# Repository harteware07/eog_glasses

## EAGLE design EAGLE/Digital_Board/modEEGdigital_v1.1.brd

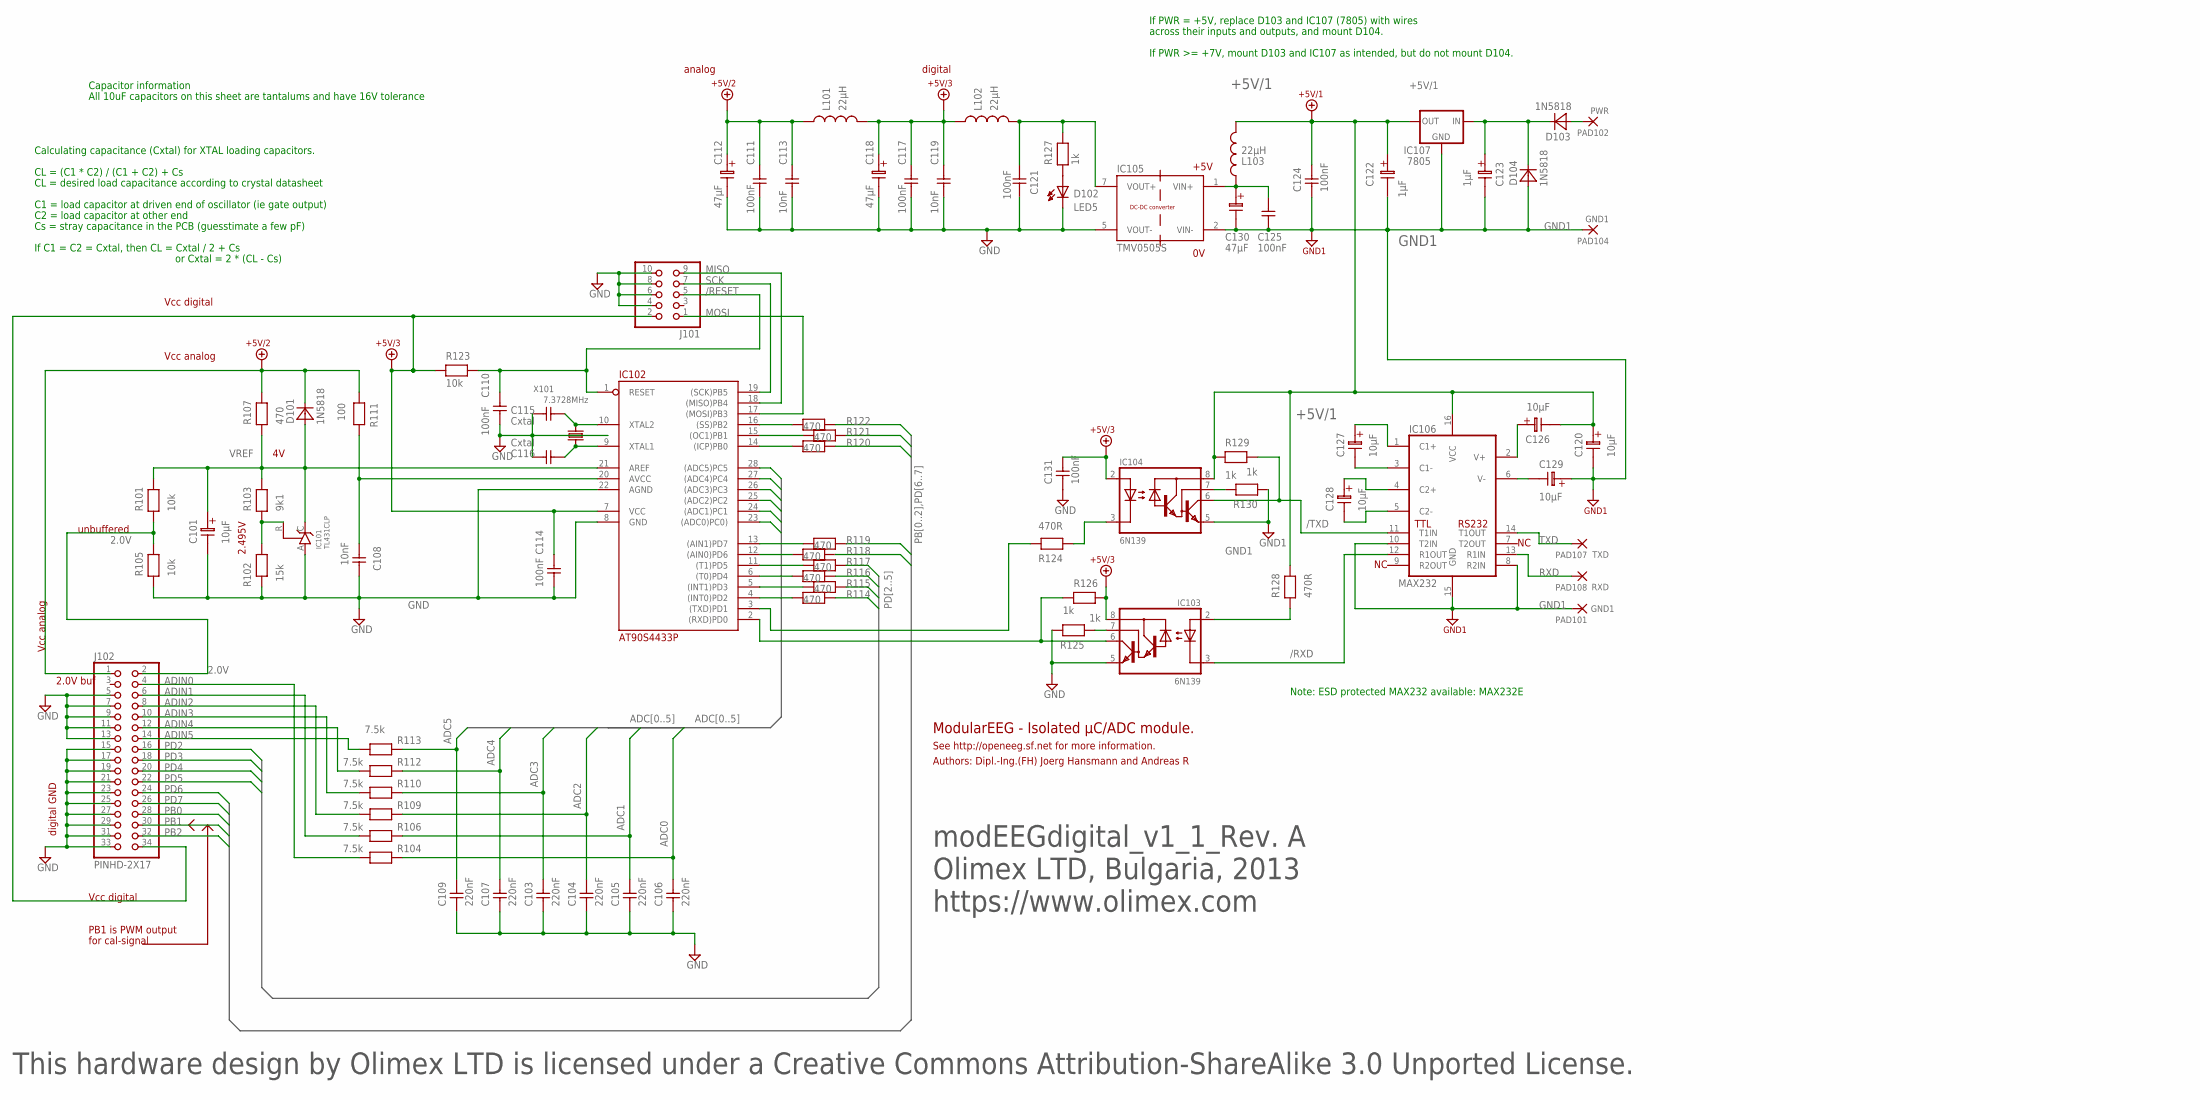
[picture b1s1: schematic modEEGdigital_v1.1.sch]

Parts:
C101, C120, C126, C127, C128, C129: 10µF; EL25B
C103, C104, C105, C106, C107, C109: 220nF; C-5
C108, C113, C119: 10nF; C-5
C110, C111, C114, C117, C125, C131: 100nF; C-5
C112, C118, C130: 47µF; EL25B
C115, C116: Cxtal; C-5
C121, C124: 100nF; C-5@1
C122, C123: 1µF; EL25B
D101: 1N5818; D-10
D102: LED5
D103, D104: 1N5818; D-12,5
IC101: TL431CLP; TO92-CLP
IC102: AT90S4433P; DIL-28/3
IC103, IC104: 6N139; DIL-08
IC105: TMV0505S; TMADCDC
IC106: MAX232; DIL-16
IC107: 7805; 78XXL_S
J101: PINHD-2X5; 2X05
J102: PINHD-2X17; 2X17
L101, L102, L103: 22µH; R-12,5
PAD101, PAD104: GND1; WIREPAD1
PAD102: PWR; WIREPAD1
PAD107: TXD; WIREPAD1
PAD108: RXD; WIREPAD1
R101, R105, R123: 10k; R-10
R102: 15k; R-10
R103: 9k1; R-10
R104, R106, R109, R110, R112, R113: 7.5k; R-10
R107, R114, R115, R116, R117, R118, R119, R120, R121, R122: 470; R-10
R111: 100; R-10
R124, R128: 470R; R-10
R125, R126, R127, R129, R130: 1k; R-10
X101: 7.3728MHz; HC49/S

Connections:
2.0V: J102.2, R101.1, R105.2
+5V/1: C120.1, C122.1, C124.2, C126.2, IC104.8 (VCC), IC106.16 (VCC), IC107.OUT, L103.2, R128.2, R129.1
+5V/2: C111.2, C112.1, C113.2, D101.2 (K), J102.1, L101.1, R107.2, R111.1
+5V/3: C114.2, C117.2, C118.1, C119.2, C131.2, IC102.7 (VCC), IC103.8 (VCC), IC104.2 (A), J101.2, J102.34, L101.2, L102.1, R123.1, R126.2
+6TO12V: C123.1, D103.2 (K), D104.2 (K), IC107.IN
/RESET: C110.2, IC102.1 (RESET), J101.5, R123.2
/RXD: IC103.3 (K), IC106.12 (R1OUT)
/TXD: IC104.6 (VO), IC106.11 (T1IN), R129.2
ADC0: C106.2, IC102.23 ((ADC0)PC0)), R104.2
ADC1: C105.2, IC102.24 ((ADC1)PC1), R106.2
ADC2: C104.2, IC102.25 ((ADC2)PC2), R109.2
ADC3: C103.2, IC102.26 ((ADC3)PC3), R110.2
ADC4: C107.2, IC102.27 ((ADC4)PC4), R112.2
ADC5: C109.2, IC102.28 ((ADC5)PC5), R113.2
ADIN0: J102.4, R104.1
ADIN1: J102.6, R106.1
ADIN2: J102.8, R109.1
ADIN3: J102.10, R110.1
ADIN4: J102.12, R112.1
ADIN5: J102.14, R113.1
AVCC: C108.2, IC102.20 (AVCC), R111.2
GND: C101.2, C103.1, C104.1, C105.1, C106.1, C107.1, C108.1, C109.1, C110.1, C111.1, C112.2, C113.1, C114.1, C115.1, C116.1, C117.1, C118.2, C119.1, C121.2, C131.1, D102.K, IC101.A, IC102.8 (GND), IC102.22 (AGND), IC103.5 (GND), IC105.5 (VOUT-), J101.4, J101.6, J101.8, J101.10, J102.5, J102.7, J102.9, J102.11, J102.13, J102.15, J102.17, J102.19, J102.21, J102.23, J102.25, J102.27, J102.29, J102.31, J102.33, R102.1, R105.1, R125.2
GND1: C120.2, C122.2, C123.2, C124.1, C125.1, C129.1, C130.2, D104.1 (A), IC104.5 (GND), IC105.2 (VIN-), IC106.8 (R2IN), IC106.10 (T2IN), IC106.15 (GND), IC107.GND, PAD101.1, PAD104.1, R130.1
MISO: IC102.18 ((MISO)PB4), J101.9
MOSI: IC102.17 ((MOSI)PB3), J101.1
unnamed: IC102.4 ((INT0)PD2), R114.1
unnamed: IC102.5 ((INT1)PD3), R115.1
unnamed: IC102.6 ((T0)PD4), R116.1
unnamed: IC101.R, R102.2, R103.1
unnamed: IC102.11 ((T1)PD5), R117.1
unnamed: IC102.12 ((AIN0)PD6), R118.1
unnamed: IC102.13 ((AIN1)PD7), R119.1
unnamed: IC104.3 (K), R124.1
unnamed: IC102.14 ((ICP)PB0), R120.1
unnamed: C116.2, IC102.9 (XTAL1), X101.1
unnamed: IC102.15 ((OC1)PB1), R121.1
unnamed: IC102.16 ((SS)PB2), R122.1
unnamed: C121.1, IC105.7 (VOUT+), L102.2, R127.2
unnamed: D102.A, R127.1
unnamed: D103.1 (A), PAD102.1
unnamed: C115.2, IC102.10 (XTAL2), X101.2
unnamed: C128.1, IC106.4 (C2+)
unnamed: C128.2, IC106.5 (C2-)
unnamed: C127.2, IC106.3 (C1-)
unnamed: C127.1, IC106.1 (C1+)
unnamed: C129.2, IC106.6 (V-)
unnamed: C126.1, IC106.2 (V+)
unnamed: C125.2, C130.1, IC105.1 (VIN+), L103.1
unnamed: IC104.7 (VB), R130.2
unnamed: IC103.7 (VB), R125.1
unnamed: IC103.2 (A), R128.1
PB0: J102.28, R120.2
PB1: J102.30, R121.2
PB2: J102.32, R122.2
PD0: IC102.2 ((RXD)PD0), IC103.6 (VO), R126.1
PD1: IC102.3 ((TXD)PD1), R124.2
PD2: J102.16, R114.2
PD3: J102.18, R115.2
PD4: J102.20, R116.2
PD5: J102.22, R117.2
PD6: J102.24, R118.2
PD7: J102.26, R119.2
RXD: IC106.13 (R1IN), PAD108.1
SCK: IC102.19 ((SCK)PB5), J101.7
TXD: IC106.14 (T1OUT), PAD107.1
VREF: C101.1, D101.1 (A), IC101.C, IC102.21 (AREF), R101.2, R103.2, R107.1

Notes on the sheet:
2.495V
unbuffered
Vcc digital
Vcc analog
TTL
RS232
+5V
analog
digital
digital GND
2.0V buf
PB1 is PWM output
for cal-signal
Authors: Dipl.-Ing.(FH) Joerg Hansmann and Andreas R
ModularEEG - Isolated µC/ADC module.
Capacitor information
All 10uF capacitors on this sheet are tantalums and have 16V tolerance
CL = (C1 * C2) / (C1 + C2) + Cs
C1 = load capacitor at driven end of oscillator (ie gate output)
C2 = load capacitor at other end
Calculating capacitance (Cxtal) for XTAL loading capacitors.
CL = desired load capacitance according to crystal datasheet
If C1 = C2 = Cxtal, then CL = Cxtal / 2 + Cs
Note: ESD protected MAX232 available: MAX232E
Cs = stray capacitance in the PCB (guesstimate a few pF)
If PWR = +5V, replace D103 and IC107 (7805) with wires
If PWR >= +7V, mount D103 and IC107 as intended, but do not mount D104.
or Cxtal = 2 * (CL - Cs)
See http://openeeg.sf.net for more information.
across their inputs and outputs, and mount D104.
modEEGdigital_v1_1_Rev. A
This hardware design by Olimex LTD is licensed under a Creative Commons Attribution-ShareAlike 3.0 Unported License.
Olimex LTD, Bulgaria, 2013
https://www.olimex.com

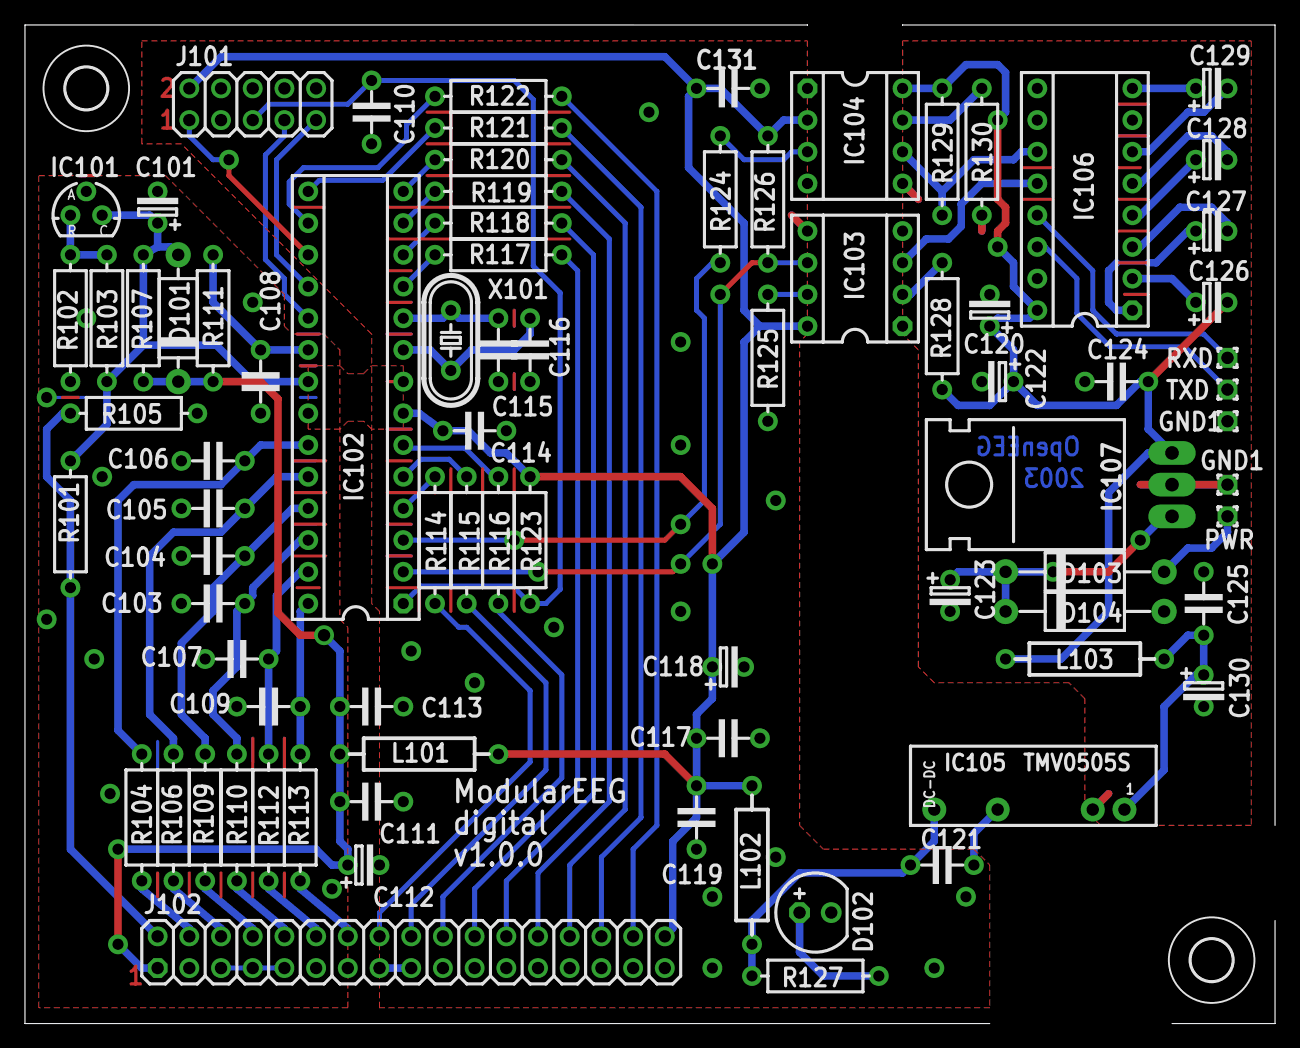
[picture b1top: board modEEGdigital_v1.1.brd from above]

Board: 2 copper layers, 100.2 x 80.0 mm, 83 parts (0 on the bottom side), 66 nets.

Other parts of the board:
U$16, U$17: 3,3

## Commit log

2016-09-26 added processing GUI project
2016-09-26 added filtering of recorded signal
2017-01-03 added loop playback of files, filter and detectors
2017-01-11 added bash scripts to fade recorded signals
2017-01-12 added eog signals
2017-02-28 added status LED
